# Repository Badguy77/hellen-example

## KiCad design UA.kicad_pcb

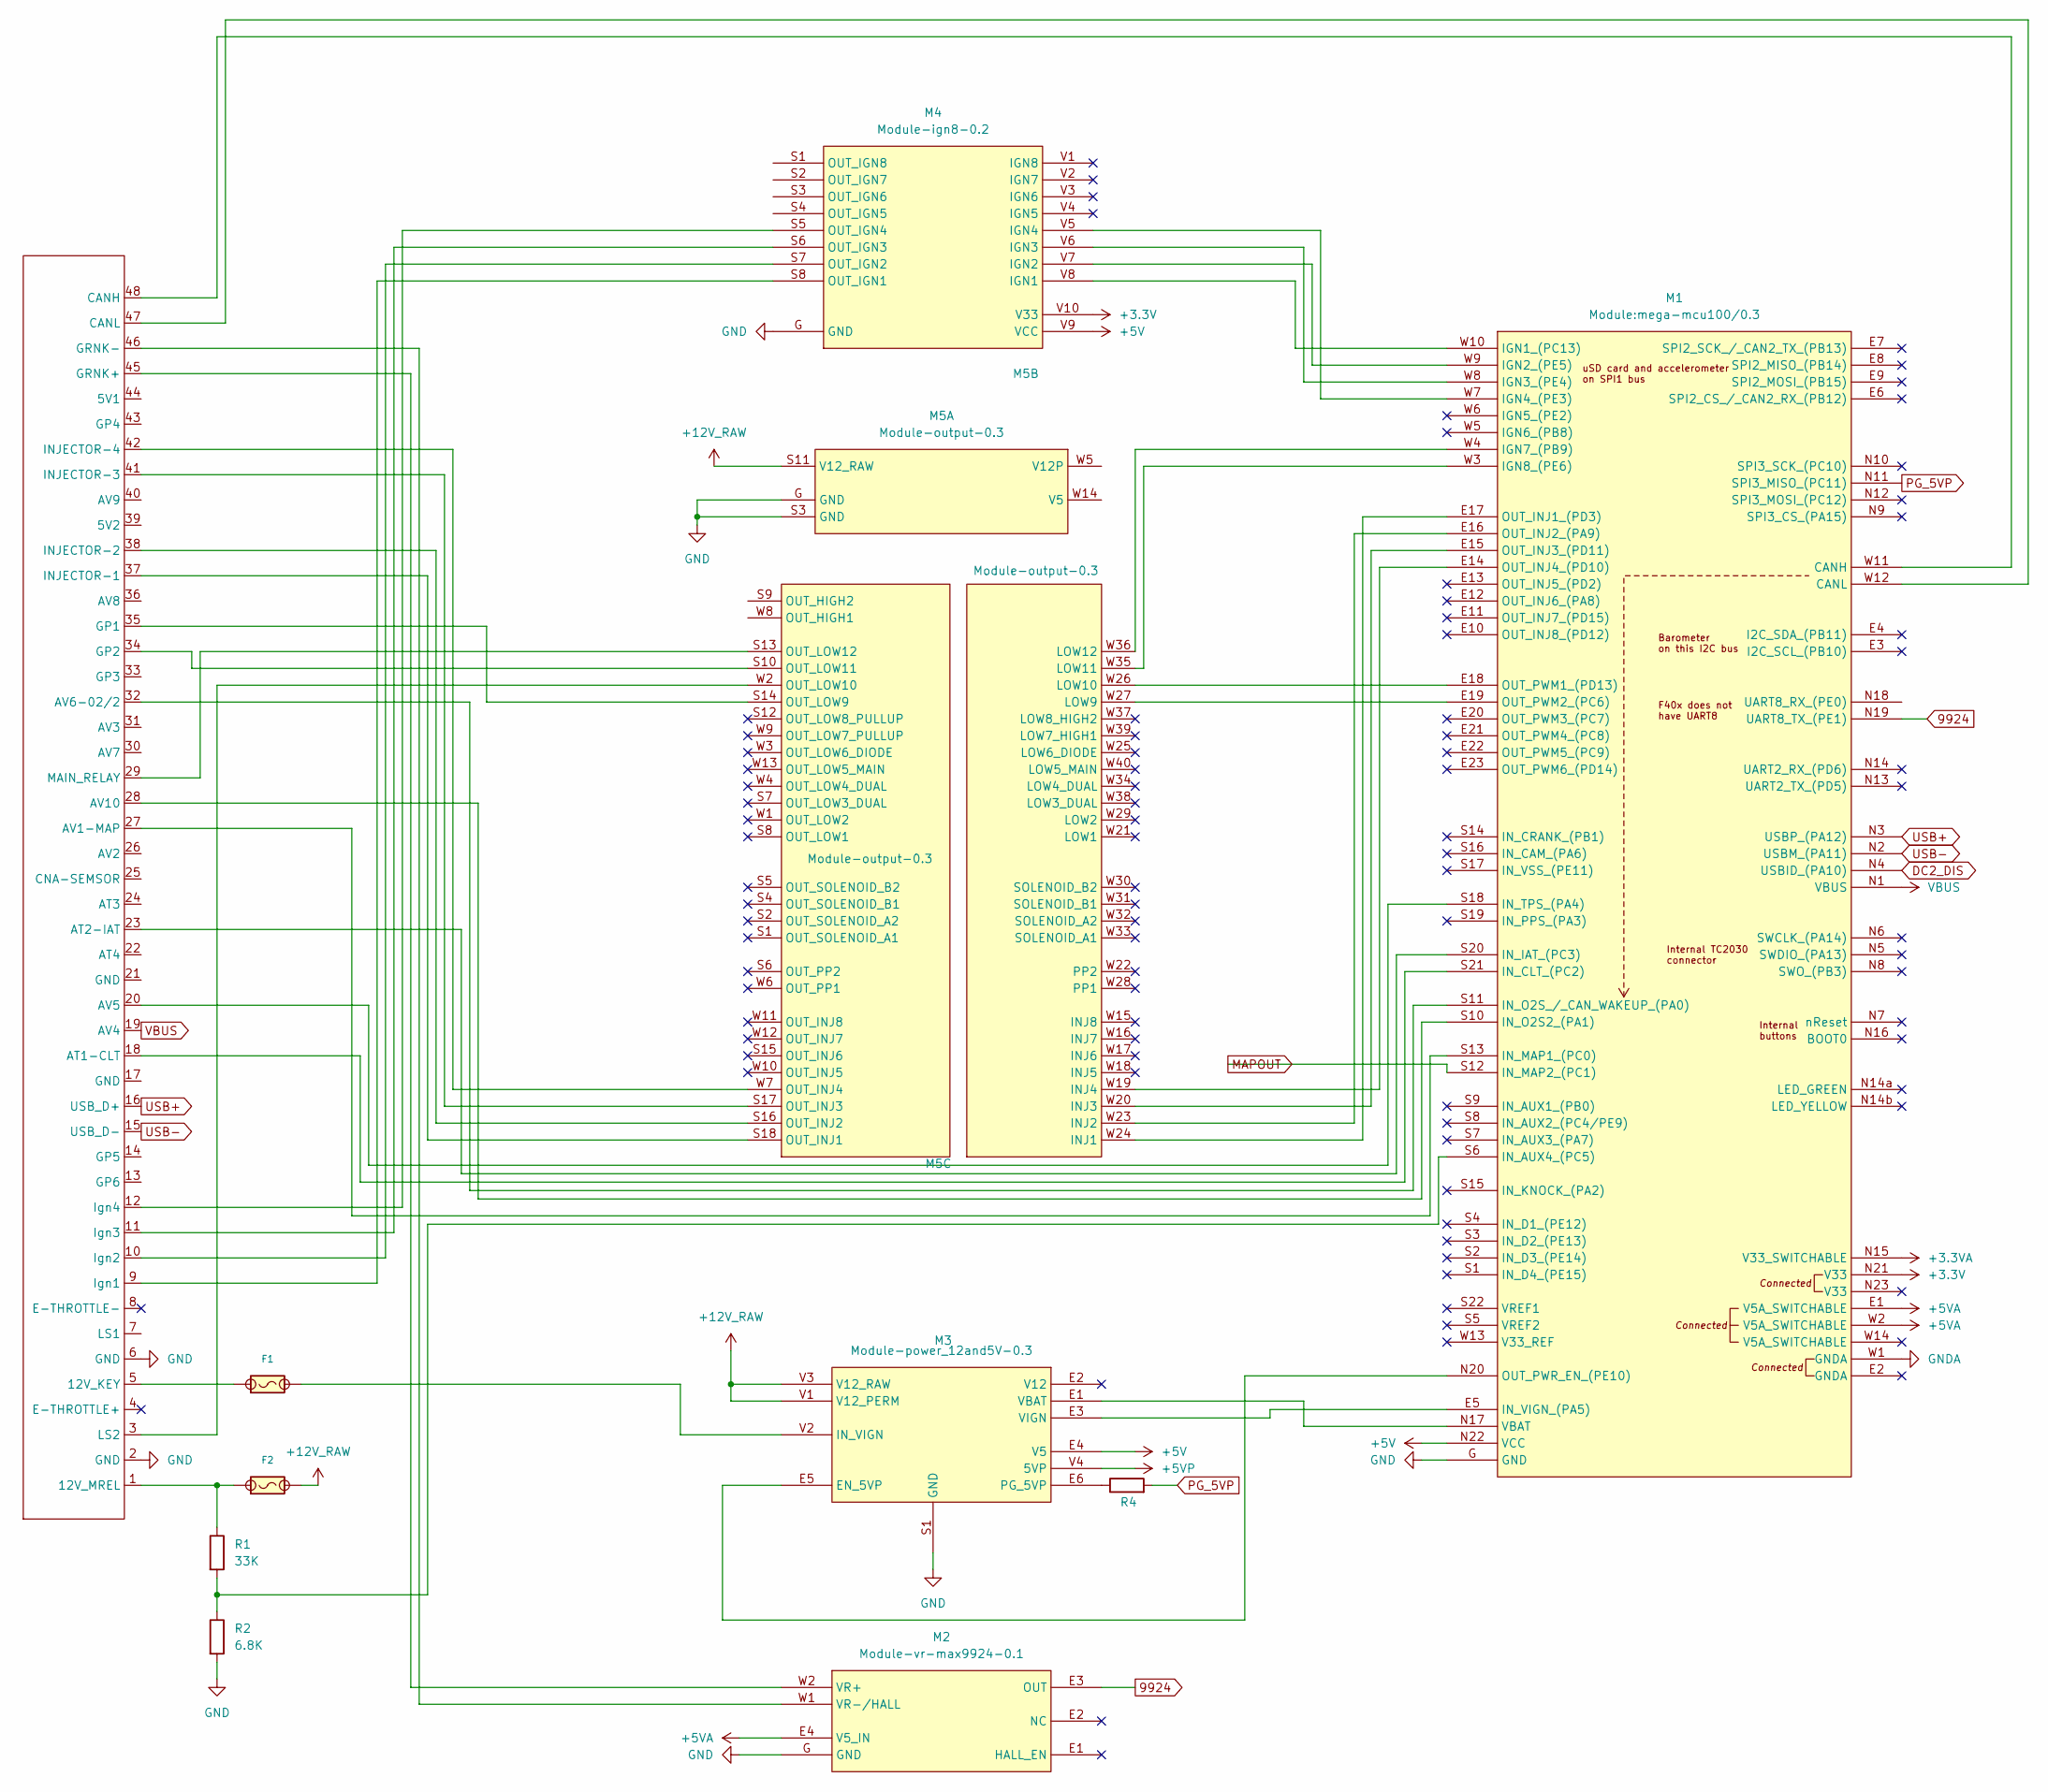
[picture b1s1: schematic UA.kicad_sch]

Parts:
F1, F2: Fuse-Pad-Pad; C_1206_3216Metric; LCSC C182446
M1: Module:mega-mcu100/0.3; mega-mcu100
M2: Module-vr-max9924-0.1; vr-max9924
M3: Module-power_12and5V-0.3; power_12and5V
M4: Module-ign8-0.2; ign8
M5: Module-output-0.3; output
R1: 33K; R_0603_1608Metric
R2: 6.8K; R_0603_1608Metric
R4: R; R_0603_1608Metric
molex_48PIN_MER1: 48PIN-ljq

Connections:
9924: M1.N19 (UART8_TX_(PE1)), M2.E3 (OUT)
+3.3V: M1.N21 (V33), M4.V10 (V33)
+3.3VA: M1.N15 (V33_SWITCHABLE)
+5V: M1.N22 (VCC), M3.E4 (V5), M4.V9 (VCC)
+5VA: M1.E1 (V5A_SWITCHABLE), M1.W2 (V5A_SWITCHABLE), M2.E4 (V5_IN)
+5VP: M3.V4 (5VP)
+12V_RAW: F2.2, M3.V1 (V12_PERM), M3.V3 (V12_RAW), M5.S11 (V12_RAW)
DC2_DIS: M1.N4 (USBID_(PA10))
GND: M1.G (GND), M2.G (GND), M3.S1 (GND), M4.G (GND), M5.G (GND), M5.S3 (GND), R2.2, molex_48PIN_MER1.2 (GND), molex_48PIN_MER1.6 (GND)
GNDA: M1.W1 (GNDA)
MAPOUT: M1.S12 (IN_MAP2_(PC1))
unnamed: M1.W11 (CANH), molex_48PIN_MER1.48 (CANH)
unnamed: M1.W12 (CANL), molex_48PIN_MER1.47 (CANL)
unnamed: M1.W10 (IGN1_(PC13)), M4.V8 (IGN1)
unnamed: M1.W9 (IGN2_(PE5)), M4.V7 (IGN2)
unnamed: M1.W8 (IGN3_(PE4)), M4.V6 (IGN3)
unnamed: M1.W7 (IGN4_(PE3)), M4.V5 (IGN4)
unnamed: M1.W4 (IGN7_(PB9)), M5.W36 (LOW12)
unnamed: M1.W3 (IGN8_(PE6)), M5.W35 (LOW11)
unnamed: M1.S6 (IN_AUX4_(PC5)), R1.2, R2.1
unnamed: M1.S21 (IN_CLT_(PC2)), molex_48PIN_MER1.18 (AT1-CLT)
unnamed: M1.S20 (IN_IAT_(PC3)), molex_48PIN_MER1.23 (AT2-IAT)
unnamed: M1.S13 (IN_MAP1_(PC0)), molex_48PIN_MER1.27 (AV1-MAP)
unnamed: M1.S10 (IN_O2S2_(PA1)), molex_48PIN_MER1.28 (AV10)
unnamed: M1.S11 (IN_O2S_/_CAN_WAKEUP_(PA0)), molex_48PIN_MER1.32 (AV6-02/2)
unnamed: M1.S18 (IN_TPS_(PA4)), molex_48PIN_MER1.20 (AV5)
unnamed: M1.E5 (IN_VIGN_(PA5)), M3.E3 (VIGN)
unnamed: M1.E17 (OUT_INJ1_(PD3)), M5.W24 (INJ1)
unnamed: M1.E16 (OUT_INJ2_(PA9)), M5.W23 (INJ2)
unnamed: M1.E15 (OUT_INJ3_(PD11)), M5.W20 (INJ3)
unnamed: M1.E14 (OUT_INJ4_(PD10)), M5.W19 (INJ4)
unnamed: M1.E18 (OUT_PWM1_(PD13)), M5.W26 (LOW10)
unnamed: M1.E19 (OUT_PWM2_(PC6)), M5.W27 (LOW9)
unnamed: M1.N20 (OUT_PWR_EN_(PE10)), M3.E5 (EN_5VP)
unnamed: M1.N17 (VBAT), M3.E1 (VBAT)
unnamed: M2.W2 (VR+), molex_48PIN_MER1.45 (GRNK+)
unnamed: M2.W1 (VR-/HALL), molex_48PIN_MER1.46 (GRNK-)
unnamed: F1.2, M3.V2 (IN_VIGN)
unnamed: M3.E6 (PG_5VP), R4.1
unnamed: M4.S8 (OUT_IGN1), molex_48PIN_MER1.9 (Ign1)
unnamed: M4.S7 (OUT_IGN2), molex_48PIN_MER1.10 (Ign2)
unnamed: M4.S6 (OUT_IGN3), molex_48PIN_MER1.11 (Ign3)
unnamed: M4.S5 (OUT_IGN4), molex_48PIN_MER1.12 (Ign4)
unnamed: M5.S18 (OUT_INJ1), molex_48PIN_MER1.37 (INJECTOR-1)
unnamed: M5.S16 (OUT_INJ2), molex_48PIN_MER1.38 (INJECTOR-2)
unnamed: M5.S17 (OUT_INJ3), molex_48PIN_MER1.41 (INJECTOR-3)
unnamed: M5.W7 (OUT_INJ4), molex_48PIN_MER1.42 (INJECTOR-4)
unnamed: M5.S14 (OUT_LOW9), molex_48PIN_MER1.35 (GP1)
unnamed: M5.W2 (OUT_LOW10), molex_48PIN_MER1.3 (LS2)
unnamed: M5.S10 (OUT_LOW11), molex_48PIN_MER1.34 (GP2)
unnamed: M5.S13 (OUT_LOW12), molex_48PIN_MER1.29 (MAIN_RELAY)
unnamed: F1.1, molex_48PIN_MER1.5 (12V_KEY)
unnamed: F2.1, R1.1, molex_48PIN_MER1.1 (12V_MREL)
PG_5VP: M1.N11 (SPI3_MISO_(PC11)), R4.2
USB+: M1.N3 (USBP_(PA12)), molex_48PIN_MER1.16 (USB_D+)
USB-: M1.N2 (USBM_(PA11)), molex_48PIN_MER1.15 (USB_D-)
VBUS: M1.N1 (VBUS), molex_48PIN_MER1.19 (AV4)

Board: 2 copper layers, 11 parts (0 on the bottom side), 52 nets, no tracks yet.

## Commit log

2025-06-20 GHA says update hellen-one
2025-06-23 GHA says update kicad6-libraries
